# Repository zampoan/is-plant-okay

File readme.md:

# Is-Plant-Okay 🌱?
## Concept
A solar-powered sensor node that uses a low-power camera and a tiny on-board ML model to detect early signs of plant disease. It will be mounted on a stake and its purpose is to continuously watch the same plant or section of crop bed. 

It will periodically take a picture every 4 hours. When it sees trouble, and will send a compact alert packet over LoRa to a base station. The farmer will receive a notification and can inspect or treat the plant before disease spreads.

Dataset to be trained on: https://www.kaggle.com/datasets/vipoooool/new-plant-diseases-dataset

ML model: https://www.nature.com/articles/s41598-025-06452-5

## Hardware
- 🧠 MCU: Arduino Nano 33 BLE Sense Rev2 
- 🔋 LiIon: 7.4 2000mAh
- ☀️ Solar power cells: 0.5W Solar Panel 55x70
- 📷 Camera: CAMERA-OV7670
- 🌡️ Temperature sensor: Arduino Nano 33 BLE Sense Rev2 (onboard HS3003)
- 🌡️ Humidity sensor: Arduino Nano 33 BLE Sense Rev2 (onboard HS3003)
- ~~🌡️ Soil moisture sensor: (Premi um option: RS485)~~
- 🖵 Screen: GRAPHIC DISPLAY TFT RGB 0.96"
- 📡 LoRa: SX1278 RA-02 (Premium option:RYLR998)
- ~~💡 Light Sensor: TSL2591~~
- ~~⚡ UV Sensor: VEML6075~~

## Software
- KiCad 9.0: Schematic diagram drawing & PCB design
- Fusion 360: Case design

# BOM:
| Hardware | Price ($USD) | QTY| Link |
| :------: | :---: | :--: | :--: |
| Arduino Nano 33 BLE Sense Rev 2 | 38.70 | 1 | https://www.digikey.com.au/en/products/detail/arduino/ABX00069/16891607?s=N4IgTCBcDaIIICEAaAGNA2AnCAugXyA
| 0.5W Solar Panel 55x70 | 6.07 | 2 | https://www.digikey.com.au/en/products/detail/seeed-technology-co-ltd/313070004/5488049?gad_source=1&gad_campaignid=22258692864&gbraid=0AAAAADrbLlhlBg2sAgWDGFOENqgOK8itr&gclid=CjwKCAjwuePGBhBZEiwAIGCVS1SN-ztdDNMpsNeNdLkv1kFB5a2T7XsfMUYFsP6d9YNnIU8SkSqs2BoCFH4QAvD_BwE&gclsrc=aw.ds
| CAMERA-OV7670 | 10.25 | 1 | https://www.digikey.com.au/en/products/detail/olimex-ltd/CAMERA-OV7670/21662189?gad_source=1&gad_campaignid=22258692864&gbraid=0AAAAADrbLlj6oJtUsNfVx1vIrDFE3BPZ1&gclid=Cj0KCQjw9JLHBhC-ARIsAK4PhcpgwkVmjjOCHtvELpGt-0733CaYN9VAK-Vob_rOJUDzvEmz226i8pQaAqYBEALw_wcB&gclsrc=aw.ds
| (Camera Alternative) Mini 2MP SPI Camera Module | 25.99 | 1 | https://core-electronics.com.au/mini-2mp-spi-camera-module-for-raspberry-pi-pico.html
| GRAPHIC DISPLAY TFT RGB 0.96" | 12.65| 1 | https://www.digikey.com.au/en/products/detail/adafruit-industries-llc/3533/7386265?_gl=1*b8bl6n*_up*MQ..*_gs*MQ..&gclid=Cj0KCQjw0Y3HBhCxARIsAN7931UClWFcKTlh2fkHoq46prUC8q0JHHVEXAIprqbeCdMH-Q-fxAHX3awaAoXnEALw_wcB&gclsrc=aw.ds&gbraid=0AAAAADrbLlg15LkEfC3epRZwz2bj5q-3L
| LORA BREAKOUT BOARD WITH ANTENNA (SX1278) | 4.12 | 2 |https://www.digikey.com.au/en/products/detail/ai-thinker/RA-01S-KIT/16688834?gad_source=1&gad_campaignid=22326148211&gbraid=0AAAAADrbLlhLN5hmf02vxdAPvPhM4dgSv&gclid=Cj0KCQjw9JLHBhC-ARIsAK4PhcreZk6yLUpkKNMcTffMBGgSn7cPre5FqczhVUk0twJjBSD5UAG_9JgaAqmoEALw_wcB&gclsrc=aw.ds
| (Lora alternative) WIO-E5 MINI DEV BRD STM32WLE5JC | 21.90 | 1 | https://www.digikey.com.au/en/products/detail/seeed-technology-co-ltd/113990939/13926228
| 18650 BATTERY PROTECTION MODULE | 3.9 | 1 | https://www.digikey.com.au/en/products/detail/dfrobot/FIT0869/15997370?gad_source=1&gad_campaignid=22258692864&gbraid=0AAAAADrbLlg15LkEfC3epRZwz2bj5q-3L&gclid=Cj0KCQjw9JLHBhC-ARIsAK4PhcrrSuu6PmTF7blXYFuWj3jp-5aErfmPy3v33kaB2AZqo8hcHLbKMqoaAtIpEALw_wcB&gclsrc=aw.ds
| BATT HOLDER 18650 2 CELL PC PIN | 5.16 | 1 | https://www.digikey.com.au/en/products/detail/mpd-memory-protection-devices/BK-18650-PC4/2330513
| SPI RTC | 27.5 | 1 | https://www.digikey.com.au/en/products/detail/sparkfun-electronics/10160/5318743?gad_source=1&gad_campaignid=17413568847&gbraid=0AAAAADrbLlhQzfR05Cs2nWnXQWMDkBFCG&gclid=Cj0KCQjwl5jHBhDHARIsAB0YqjxafYtF9_N9fzqCNYOEMk2vtOCLYpYshzIofeoXUn1t9SEJgBJjOhwaAnBeEALw_wcB&gclsrc=aw.ds

## Inspiration
https://blog.arduino.cc/2020/06/24/machine-vision-with-low-cost-camera-modules/
https://cdn-learn.adafruit.com/downloads/pdf/adafruit-mini-tft-0-dot-96-inch-180x60-breakout.pdf
https://files.seeedstudio.com/products/317990687/res/LoRa-E5%20module%20datasheet_V1.0.pdf

# Project Timeline
## Stage 0: Project Conceptualization
Stage 0 focuses on identifying the key skills to develop for this project. My goal was to deepen my understanding of wireless communication and explore how to integrate machine learning into embedded devices. I was particularly interested in how these technologies could support farmers and forest rangers in monitoring crops and plants across large, diverse environment. My goal was to make it as cheap as possible and require little human interaction once placed.

## Stage 1a: Development board stage
Stage 1a involves selecting different components to interface with each other. The most important element was the microcontroller, and I choose the Arduino Nano 33 BLE Sense V2 for its built in sensor capabilities, community support and access to TF-lite as an edge-ml solution.

The next was selecting a camera, I needed a camera that I could use off the shelf quickly for developing. Originally HM0360-MWA-00FP963 was selected, but I found it difficult to find a dev board for it. So the OV7670 was selected instead.

Similiar to the camera, SX1278 RA-02 module was selected because a dev board was available, and the DS3234 was chosen because SPI is the common protocol that is being used.

## Stage 1b: Developing the model
The model that is being used is based of the paper: [AI and IoT-powered edge device optimized for crop pest and disease detection](https://www.nature.com/articles/s41598-025-06452-5) and is called Tiny-LiteNet. It was chosen because of its use case matched  and identifiable metrics used to train and test the model. 

The model is made from scratch and is trained on a different dataset and uses a pretrained MobileNetv2 model as a teacher model. Tiny-LiteNet utilises six squeeze-and-excitation (SE) depthwise blocks to enhance feature representation, reduce compute cost and improve accuracy combined. The size of this model is 1.2Mb.

Tiny-LiteNet architecture:

## Stage 2a: PCB design

## Stage 2b: CAD design

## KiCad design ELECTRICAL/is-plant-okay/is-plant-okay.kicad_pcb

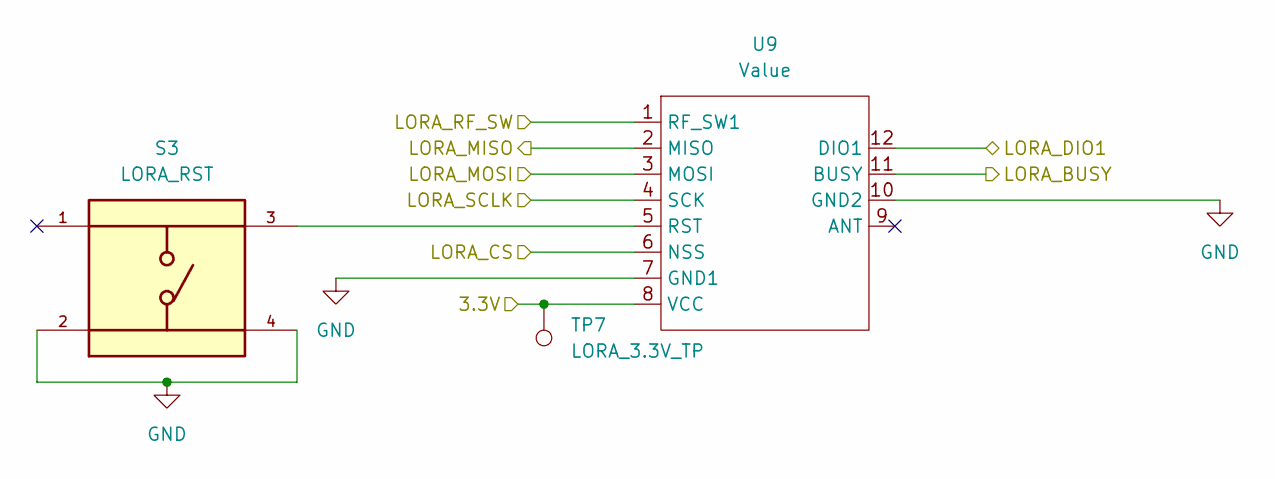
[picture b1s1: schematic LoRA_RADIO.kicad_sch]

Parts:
S3: LORA_RST; SW_TS04-66-55-BK-260-SMT; MFG PART # TS04-66-55-BK-260-SMT
TP7: LORA_3.3V_TP; TestPoint_Keystone_5000-5004_Miniature
U9: Value; Wio-SX1262 PCB Package; MFG PART # 114993390

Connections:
/3.3V: TP7.1, U9.8 (VCC); also elsewhere on the board
/LORA_BUSY: U9.11 (BUSY); also elsewhere on the board
/LORA_CS: U9.6 (NSS); also elsewhere on the board
/LORA_DIO1: U9.12 (DIO1); also elsewhere on the board
/LORA_MISO: U9.2 (MISO); also elsewhere on the board
/LORA_MOSI: U9.3 (MOSI); also elsewhere on the board
/LORA_RF_SW: U9.1 (RF_SW1); also elsewhere on the board
/LORA_SCLK: U9.4 (SCK); also elsewhere on the board
GND: S3.2, S3.4, U9.7 (GND1), U9.10 (GND2); also elsewhere on the board
unnamed: S3.3, U9.5 (RST)

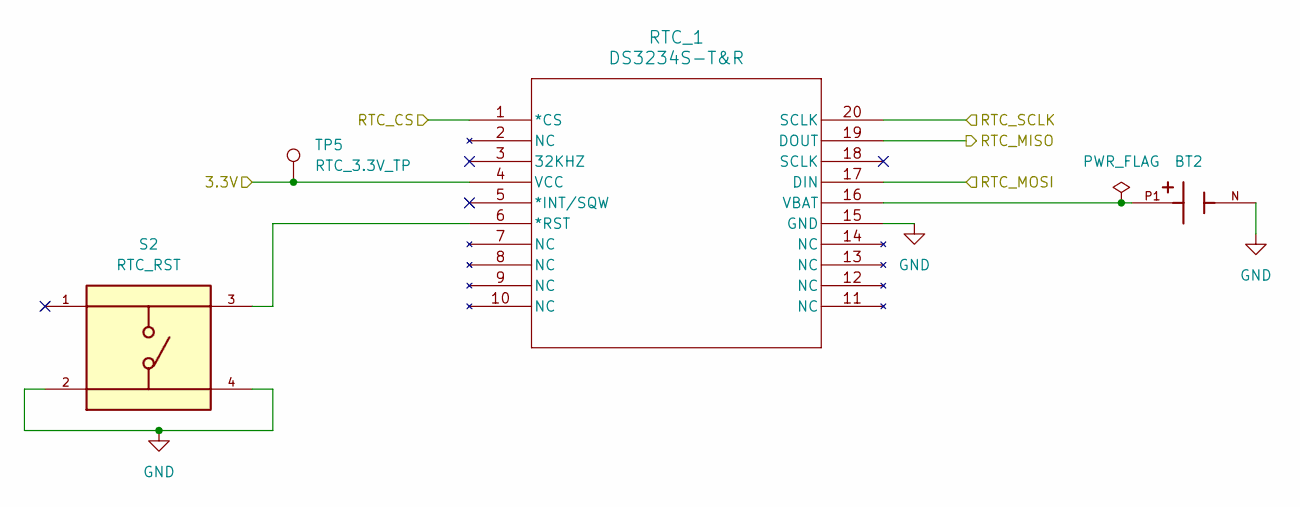
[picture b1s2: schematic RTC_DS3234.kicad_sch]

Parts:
BT2: BAT-HLD-003-SMT; BAT_BAT-HLD-003-SMT; MFG PART # BAT-HLD-003-SMT
RTC_1: DS3234S-T&R; 21-0042O_W20-H2_MXM-L; MFG PART # DS3234S#
S2: RTC_RST; SW_TS04-66-55-BK-260-SMT; MFG PART # TS04-66-55-BK-260-SMT
TP5: RTC_3.3V_TP; TestPoint_Keystone_5000-5004_Miniature

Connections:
/3.3V: RTC_1.4 (VCC), TP5.1; also elsewhere on the board
/LORA_MISO: RTC_1.19 (DOUT); also elsewhere on the board
/LORA_MOSI: RTC_1.17 (DIN); also elsewhere on the board
/LORA_SCLK: RTC_1.20 (SCLK); also elsewhere on the board
/RTC_CS: RTC_1.1 (*CS); also elsewhere on the board
GND: BT2.N, RTC_1.15 (GND), S2.2, S2.4; also elsewhere on the board
unnamed: RTC_1.6 (*RST), S2.3
unnamed: BT2.P1, RTC_1.16 (VBAT)

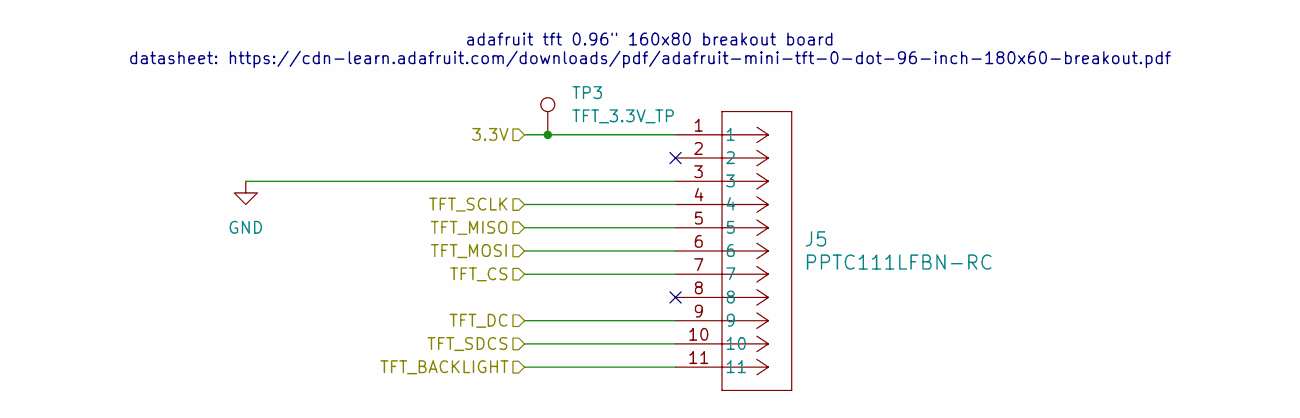
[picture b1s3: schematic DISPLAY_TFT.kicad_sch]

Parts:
J5: PPTC111LFBN-RC; CONN11_PPPN111_SUL; MFG PART # PPTC111LFBN-RC
TP3: TFT_3.3V_TP; TestPoint_Keystone_5000-5004_Miniature

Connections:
/3.3V: J5.1, TP3.1; also elsewhere on the board
/BACKLIGHT: J5.11; also elsewhere on the board
/LORA_MISO: J5.5; also elsewhere on the board
/LORA_MOSI: J5.6; also elsewhere on the board
/LORA_SCLK: J5.4; also elsewhere on the board
/TFT_CS: J5.7; also elsewhere on the board
/TFT_DC: J5.9; also elsewhere on the board
/TFT_SDCS: J5.10; also elsewhere on the board
GND: J5.3; also elsewhere on the board

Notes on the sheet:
adafruit tft 0.96" 160x80 breakout board datasheet: https://cdn-learn.adafruit.com/downloads/pdf/adafruit-mini-tft-0-dot-96-inch-180x60-breakout.pdf

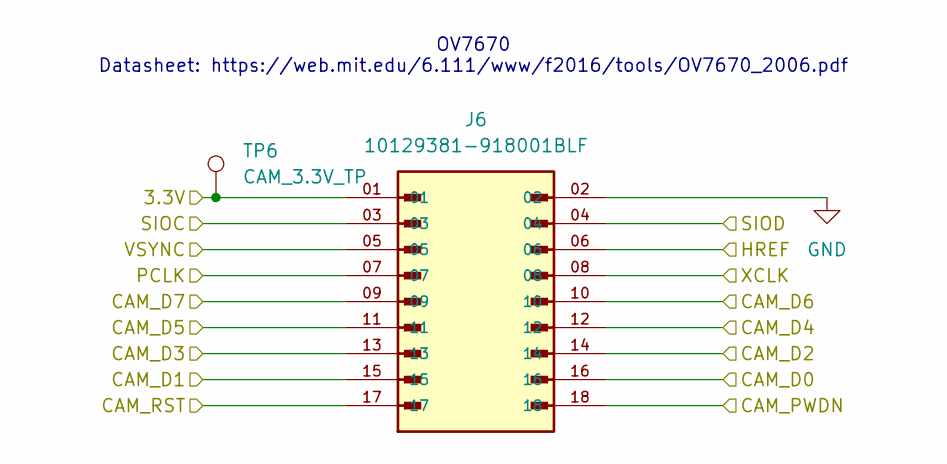
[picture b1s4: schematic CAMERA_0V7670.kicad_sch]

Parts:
J6: 10129381-918001BLF; AMPHENOL_10129381-918001BLF; MFG PART # 10129381-918001BLF
TP6: CAM_3.3V_TP; TestPoint_Keystone_5000-5004_Miniature

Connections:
/3.3V: J6.01, TP6.1; also elsewhere on the board
/CAM_D0: J6.16; also elsewhere on the board
/CAM_D1: J6.15; also elsewhere on the board
/CAM_D2: J6.14; also elsewhere on the board
/CAM_D3: J6.13; also elsewhere on the board
/CAM_D4: J6.12; also elsewhere on the board
/CAM_D5: J6.11; also elsewhere on the board
/CAM_D6: J6.10; also elsewhere on the board
/CAM_D7: J6.09; also elsewhere on the board
/CAM_PWDN: J6.18; also elsewhere on the board
/CAM_RST: J6.17; also elsewhere on the board
/HREF: J6.06; also elsewhere on the board
/PCLK: J6.07; also elsewhere on the board
/SIOC: J6.03; also elsewhere on the board
/SIOD: J6.04; also elsewhere on the board
/VSYNC: J6.05; also elsewhere on the board
/XCLK: J6.08; also elsewhere on the board
GND: J6.02; also elsewhere on the board

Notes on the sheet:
OV7670 Datasheet: https://web.mit.edu/6.111/www/f2016/tools/OV7670_2006.pdf

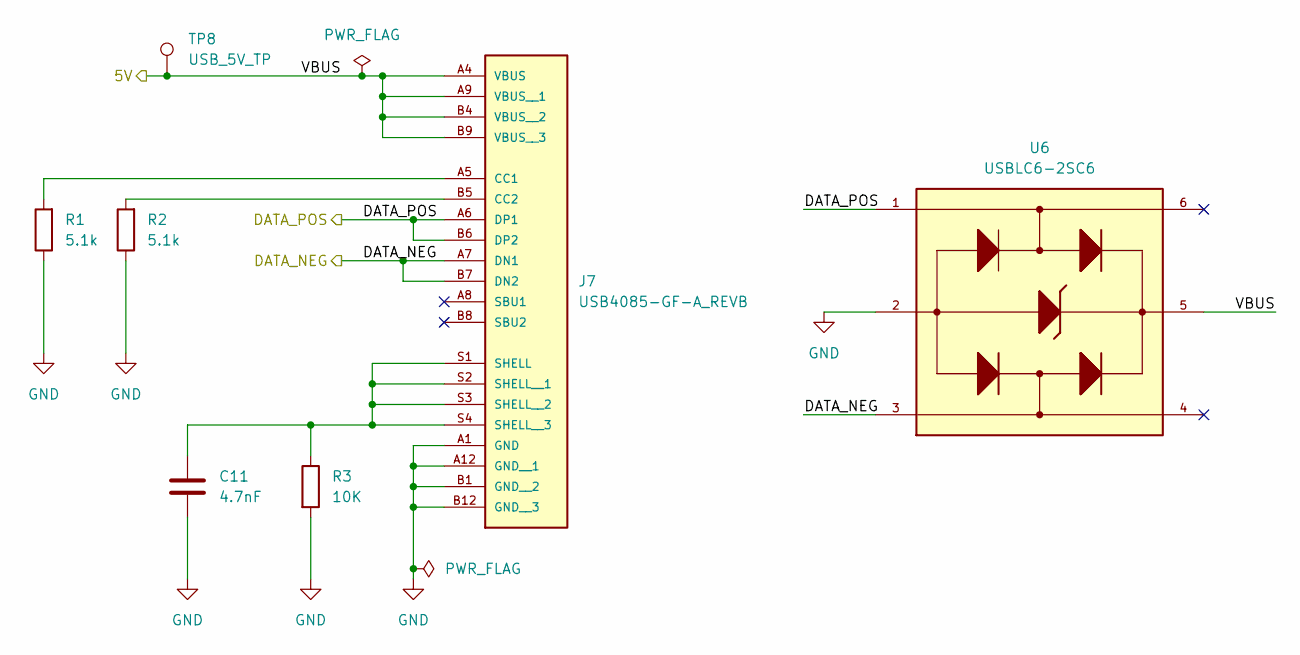
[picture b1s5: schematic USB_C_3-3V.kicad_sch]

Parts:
C11: 4.7nF; CAPC1005X55N; MFG PART # CL05B104KO5NNNC
J7: USB4085-GF-A_REVB; GCT_USB4085-GF-A_REVB; MFG PART # USB4085-GF-A
R1, R2: 5.1k; RC0805JR-075K1L; MFG PART # RC0805JR-075K1L
R3: 10K; RC0805FR-7W10KL; MFG PART # RC0805FR-7W10KL
TP8: USB_5V_TP; TestPoint_Keystone_5000-5004_Miniature
U6: USBLC6-2SC6; SOT95P280X145-6N; MFG PART # USBLC6-2SC6

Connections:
/5V: J7.A4 (VBUS), J7.A9 (VBUS__1), J7.B4 (VBUS__2), J7.B9 (VBUS__3), TP8.1, U6.5; also elsewhere on the board
/DATA_NEG: J7.A7 (DN1), J7.B7 (DN2), U6.3; also elsewhere on the board
/DATA_POS: J7.A6 (DP1), J7.B6 (DP2), U6.1; also elsewhere on the board
GND: C11.2, J7.A1 (GND), J7.A12 (GND__1), J7.B1 (GND__2), J7.B12 (GND__3), R1.1, R2.1, R3.2, U6.2; also elsewhere on the board
unnamed: J7.A5 (CC1), R1.2
unnamed: J7.B5 (CC2), R2.2
unnamed: C11.1, J7.S1 (SHELL), J7.S2 (SHELL__1), J7.S3 (SHELL__2), J7.S4 (SHELL__3), R3.1

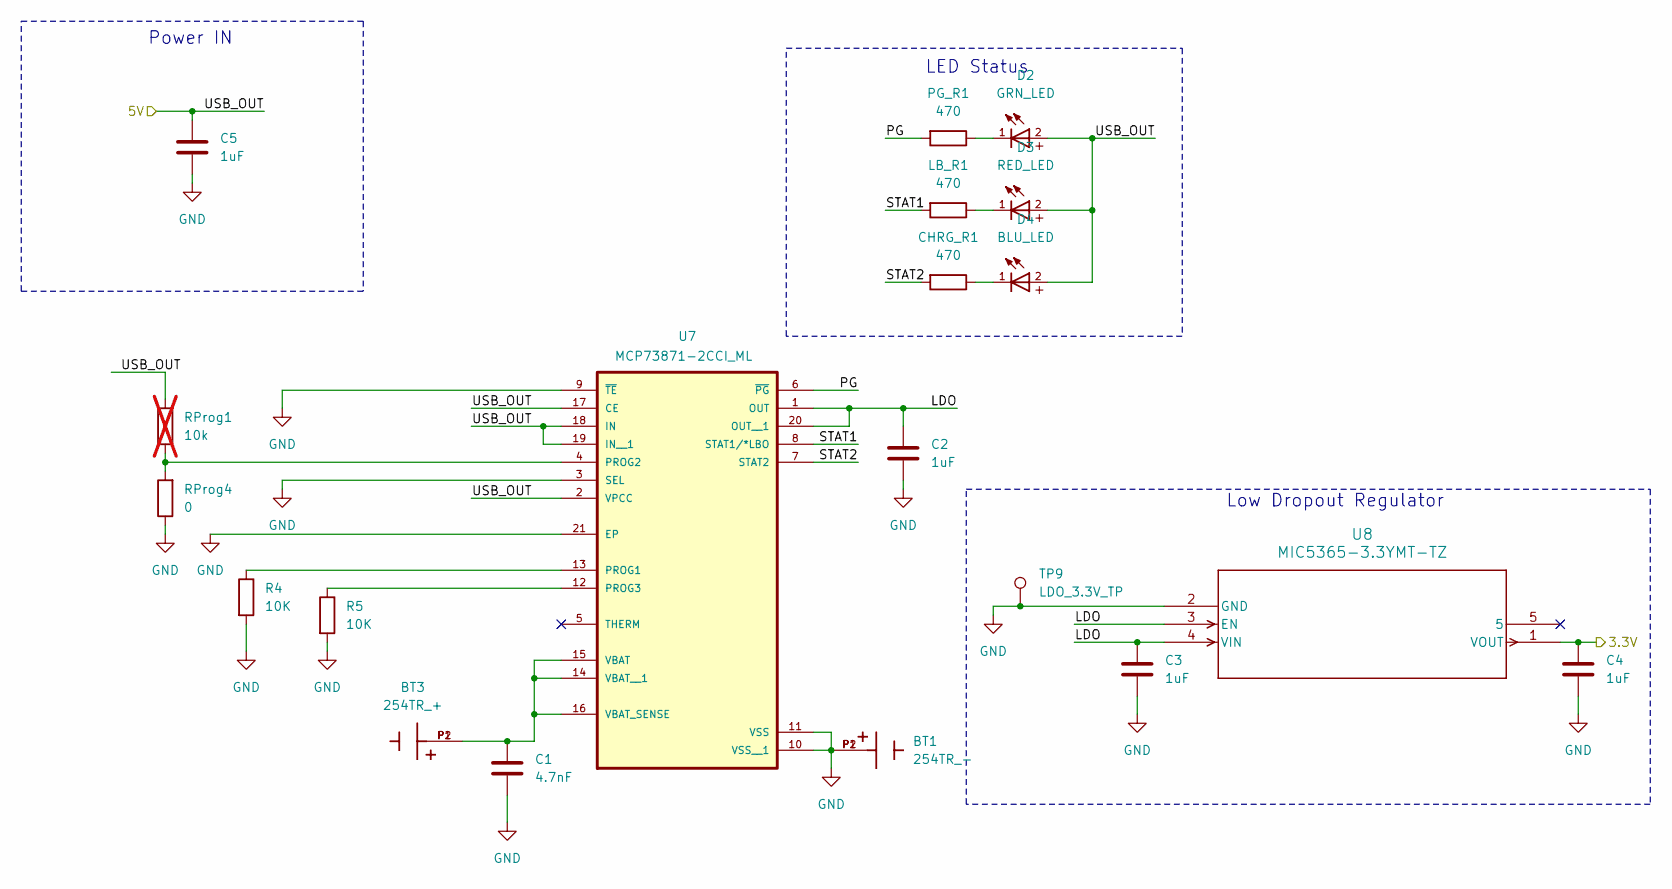
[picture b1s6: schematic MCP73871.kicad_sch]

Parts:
BT1: 254TR_-; BAT_254TR; MFG PART # 254TR
BT3: 254TR_+; BAT_254TR; MFG PART # 254TR
C1: 4.7nF; CAPC1005X55N; MFG PART # CL05B104KO5NNNC
C2, C3, C4, C5: 1uF; CAPC3216X180N; MFG PART # CL31B105KBHNNNE
CHRG_R1: 470; RESC2012X65N
D2: GRN_LED; 150120GS75000; MFG PART # 150120GS75000
D3: RED_LED; 150120GS75000; MFG PART # 150120RS75000
D4: BLU_LED; 150120GS75000; MFG PART # 150120BS75000
LB_R1: 470; RESC2012X65N
PG_R1: 470; RESC2012X65N
R4, R5: 10K; RC0805FR-7W10KL; MFG PART # RC0805FR-7W10KL
RProg1: 10k; RES_ZOR25_6P3X2P3_YAG; MFG PART # ZOR-25-B-52-0R; not fitted
RProg4: 0; RES_ZOR25_6P3X2P3_YAG; MFG PART # ZOR-25-B-52-0R
TP9: LDO_3.3V_TP; TestPoint_Keystone_5000-5004_Miniature
U7: MCP73871-2CCI_ML; QFN50P400X400X100-21N; MFG PART # MCP73871-2CCI/ML
U8: MIC5365-3.3YMT-TZ; TMLF-4_MCH; MFG PART # MIC5365-3.3YMT-TZ

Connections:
/3.3V: C4.1, U8.1 (VOUT); also elsewhere on the board
/5V: C5.1, D2.2, D3.2, D4.2, RProg1.2, U7.2 (VPCC), U7.17 (CE), U7.18 (IN), U7.19 (IN__1); also elsewhere on the board
/MCP73871/LDO: C2.1, C3.1, U7.1 (OUT), U7.20 (OUT__1), U8.3 (EN), U8.4 (VIN)
/MCP73871/PG: PG_R1.2, U7.6 (~PG)
/MCP73871/STAT1: LB_R1.2, U7.8 (STAT1/*LBO)
/MCP73871/STAT2: CHRG_R1.2, U7.7 (STAT2)
GND: BT1.P1, BT1.P2, C1.2, C2.2, C3.2, C4.2, C5.2, R4.2, R5.2, RProg4.1, TP9.1, U7.3 (SEL), U7.9 (~TE), U7.10 (VSS__1), U7.11 (VSS), U7.21 (EP), U8.2 (GND); also elsewhere on the board
unnamed: CHRG_R1.1, D4.1
unnamed: D2.1, PG_R1.1
unnamed: D3.1, LB_R1.1
unnamed: R4.1, U7.13 (PROG1)
unnamed: RProg1.1, RProg4.2, U7.4 (PROG2)
unnamed: R5.1, U7.12 (PROG3)
unnamed: BT3.P1, BT3.P2, C1.1, U7.14 (VBAT__1), U7.15 (VBAT), U7.16 (VBAT_SENSE)

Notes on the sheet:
Low Dropout Regulator
LED Status
Power IN

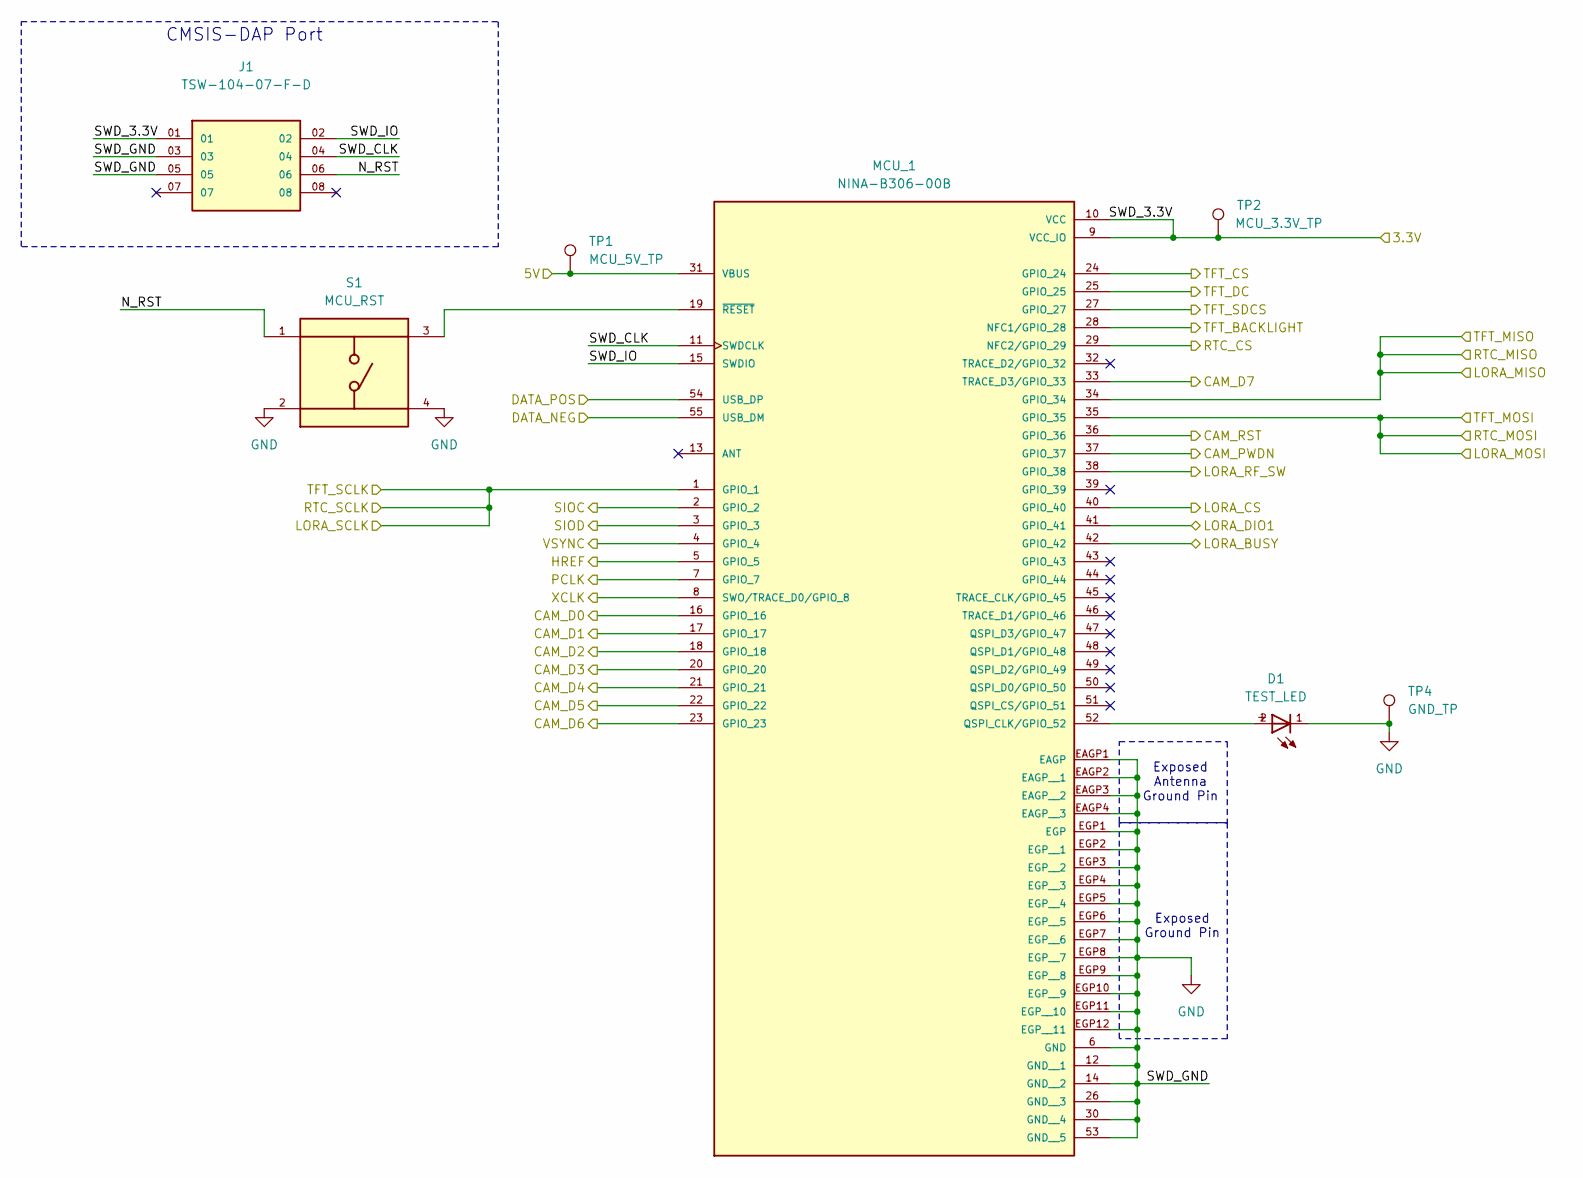
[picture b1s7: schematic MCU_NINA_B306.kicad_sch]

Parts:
D1: TEST_LED; 150120GS75000; MFG PART # 150120GS75000
J1: TSW-104-07-F-D; SAMTEC_TSW-104-07-F-D
MCU_1: NINA-B306-00B; XCVR_NINA-B306-00B; MFG PART # NINA-B306-01B
S1: MCU_RST; SW_TS04-66-55-BK-260-SMT; MFG PART # TS04-66-55-BK-260-SMT
TP1: MCU_5V_TP; TestPoint_Keystone_5000-5004_Miniature
TP2: MCU_3.3V_TP; TestPoint_Keystone_5000-5004_Miniature
TP4: GND_TP; TestPoint_Keystone_5000-5004_Miniature

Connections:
/3.3V: J1.01, MCU_1.9 (VCC_IO), MCU_1.10 (VCC), TP2.1; also elsewhere on the board
/5V: MCU_1.31 (VBUS), TP1.1; also elsewhere on the board
/BACKLIGHT: MCU_1.28 (NFC1/GPIO_28); also elsewhere on the board
/CAM_D0: MCU_1.16 (GPIO_16); also elsewhere on the board
/CAM_D1: MCU_1.17 (GPIO_17); also elsewhere on the board
/CAM_D2: MCU_1.18 (GPIO_18); also elsewhere on the board
/CAM_D3: MCU_1.20 (GPIO_20); also elsewhere on the board
/CAM_D4: MCU_1.21 (GPIO_21); also elsewhere on the board
/CAM_D5: MCU_1.22 (GPIO_22); also elsewhere on the board
/CAM_D6: MCU_1.23 (GPIO_23); also elsewhere on the board
/CAM_D7: MCU_1.33 (TRACE_D3/GPIO_33); also elsewhere on the board
/CAM_PWDN: MCU_1.37 (GPIO_37); also elsewhere on the board
/CAM_RST: MCU_1.36 (GPIO_36); also elsewhere on the board
/DATA_NEG: MCU_1.55 (USB_DM); also elsewhere on the board
/DATA_POS: MCU_1.54 (USB_DP); also elsewhere on the board
/HREF: MCU_1.5 (GPIO_5); also elsewhere on the board
/LORA_BUSY: MCU_1.42 (GPIO_42); also elsewhere on the board
/LORA_CS: MCU_1.40 (GPIO_40); also elsewhere on the board
/LORA_DIO1: MCU_1.41 (GPIO_41); also elsewhere on the board
/LORA_MISO: MCU_1.34 (GPIO_34); also elsewhere on the board
/LORA_MOSI: MCU_1.35 (GPIO_35); also elsewhere on the board
/LORA_RF_SW: MCU_1.38 (GPIO_38); also elsewhere on the board
/LORA_SCLK: MCU_1.1 (GPIO_1); also elsewhere on the board
/MCU_NINA_B306/N_RST: J1.06, S1.1
/MCU_NINA_B306/SWD_CLK: J1.04, MCU_1.11 (SWDCLK)
/MCU_NINA_B306/SWD_IO: J1.02, MCU_1.15 (SWDIO)
/PCLK: MCU_1.7 (GPIO_7); also elsewhere on the board
/RTC_CS: MCU_1.29 (NFC2/GPIO_29); also elsewhere on the board
/SIOC: MCU_1.2 (GPIO_2); also elsewhere on the board
/SIOD: MCU_1.3 (GPIO_3); also elsewhere on the board
/TFT_CS: MCU_1.24 (GPIO_24); also elsewhere on the board
/TFT_DC: MCU_1.25 (GPIO_25); also elsewhere on the board
/TFT_SDCS: MCU_1.27 (GPIO_27); also elsewhere on the board
/VSYNC: MCU_1.4 (GPIO_4); also elsewhere on the board
/XCLK: MCU_1.8 (SWO/TRACE_D0/GPIO_8); also elsewhere on the board
GND: D1.1, J1.03, J1.05, MCU_1.6 (GND), MCU_1.12 (GND__1), MCU_1.14 (GND__2), MCU_1.26 (GND__3), MCU_1.30 (GND__4), MCU_1.53 (GND__5), MCU_1.EAGP1 (EAGP), MCU_1.EAGP2 (EAGP__1), MCU_1.EAGP3 (EAGP__2), MCU_1.EAGP4 (EAGP__3), MCU_1.EGP1 (EGP), MCU_1.EGP2 (EGP__1), MCU_1.EGP3 (EGP__2), MCU_1.EGP4 (EGP__3), MCU_1.EGP5 (EGP__4), MCU_1.EGP6 (EGP__5), MCU_1.EGP7 (EGP__6), MCU_1.EGP8 (EGP__7), MCU_1.EGP9 (EGP__8), MCU_1.EGP10 (EGP__9), MCU_1.EGP11 (EGP__10), MCU_1.EGP12 (EGP__11), S1.2, S1.4, TP4.1; also elsewhere on the board
unnamed: D1.2, MCU_1.52 (QSPI_CLK/GPIO_52)
unnamed: MCU_1.19 (~RESET), S1.3

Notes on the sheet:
Exposed Antenna Ground Pin
Exposed Ground Pin
CMSIS-DAP Port

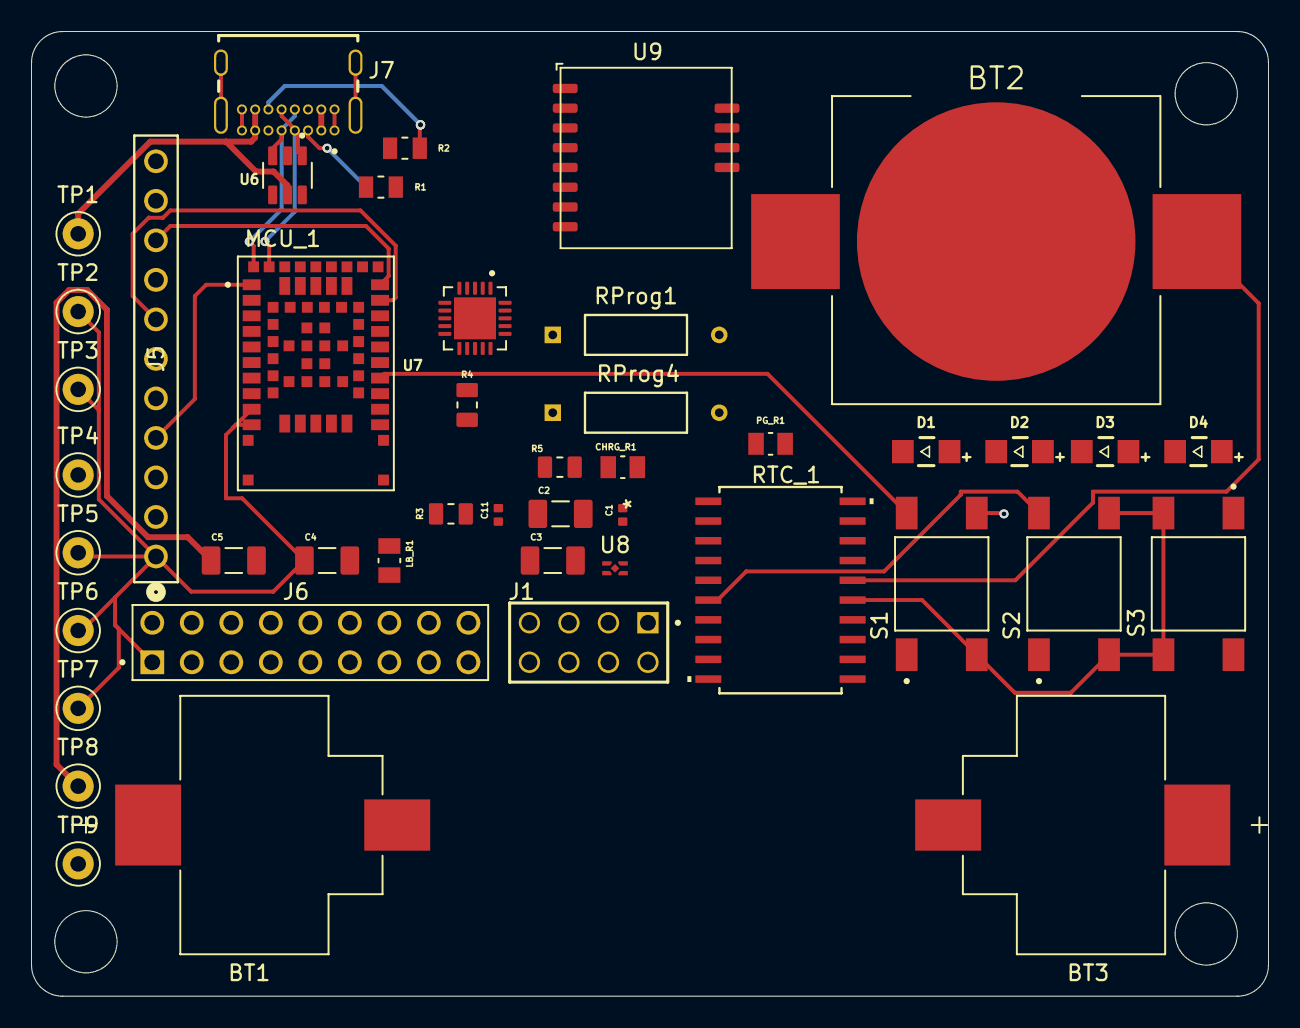
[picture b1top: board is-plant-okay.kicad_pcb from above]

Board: 2 copper layers, 79.5 x 62.0 mm, 45 parts (0 on the bottom side), 55 nets.

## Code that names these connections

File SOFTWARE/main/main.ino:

/*
    Before starting, install following libraries:
        - adafruit_gfx
        - adafruit_st7735
        - arduino_hs300x
        - arduino_bmi270_bmm150
        - arduino_LPS22HB
        - ds3231

*/
#include <SPI.h>
#include <Adafruit_GFX.h>
#include <Adafruit_ST7735.h> // using 0.96" 160x80 tft display
#include <Arduino_HS300x.h>
#include <DS3231.h>
#include <time.h>

// Pinouts
#define CAM_D0 D0
#define CAM_D1 D1
#define CAM_D2 D2
#define CAM_D3 D3
#define CAM_D4 D4
#define CAM_D5 D5
#define CAM_D6 D6
#define CAM_D7 D7
#define CAM_VSYNC D8
#define CAM_XCLK D9 
#define CAM_HREF D10
#define TFT_DC A0
#define LORA_CS A1
#define LORA_RST A2
#define TFT_CS A3
#define CAM_SIOD A4
#define CAM_SIOC A5
#define RTC_CS A6
#define CAM_PCLK A7
#define UNUSED_PIN -1

#define DEBUG
#ifdef DEBUG
    #define DEBUG_PRINT(x) Serial.print(x)
    #define DEBUG_PRINTLN(x) Serial.println(x) 
#else
    #define DEBUG_PRINT(x) 
    #define DEBUG_PRINTLN(x) 
#endif

// tft screen
Adafruit_ST7735 tft = Adafruit_ST7735(TFT_CS, TFT_DC, UNUSED_PIN);

// DS3231 rtc
// RTClib myRTC;
// DateTime now = myRTC.now();

// temperature and humidity sensor
float old_temp = 0;
float old_hum = 0;

void showTemperatureHumidity(void){
    float temperature = HS300x.readTemperature();
    float humidity = HS300x.readHumidity();

    if (abs(old_temp - temperature) >= 0.5 || abs(old_hum - humidity) >= 1){
        DEBUG_PRINT("Temperature: ");
        DEBUG_PRINTLN(temperature);

        DEBUG_PRINT("Humidity: ");
        DEBUG_PRINTLN(humidity);
        DEBUG_PRINTLN(" %");

        delay(500);
    }
}

void drawText(char *text, uint16_t textColor, uint8_t xCursor, uint8_t yCursor){
    tft.setRotation(1);
    tft.setCursor(xCursor, yCursor);
    tft.setTextColor(textColor, ST7735_BLACK);
    tft.setTextWrap(true);
    tft.print(text);
}

void setup() {
    Serial.begin(11600);
    SPI.begin();

    if (!HS300x.begin()){
        DEBUG_PRINTLN("Failed to init HS300x!");
    } 

    // Camera Pins
    pinMode(CAM_SIOD, INPUT); // Serial ubterface data I/o
    pinMode(CAM_SIOC, INPUT); // Serial clock
    pinMode(CAM_D0, OUTPUT); 
    pinMode(CAM_D1, OUTPUT);
    pinMode(CAM_D2, OUTPUT);
    pinMode(CAM_D3, OUTPUT);
    pinMode(CAM_D4, OUTPUT);
    pinMode(CAM_D5, OUTPUT);
    pinMode(CAM_D6, OUTPUT);
    pinMode(CAM_D7, OUTPUT);
    pinMode(CAM_VSYNC, OUTPUT); // vertical sync output
    pinMode(CAM_HREF, OUTPUT); // href output
    pinMode(CAM_PCLK, OUTPUT); // pixel clock output
    pinMode(CAM_XCLK, OUTPUT); // system clock output


    // LoRa Module Pins
    pinMode(LORA_CS, OUTPUT);
    pinMode(LORA_RST, OUTPUT);

    // TFT Screen Pins
    pinMode(TFT_CS, OUTPUT);
    tft.initR(INITR_MINI160x80);
    tft.fillScreen(ST7735_BLACK);

    // RTC Pins
    pinMode(RTC_CS, OUTPUT);

    delay(3000);
    DEBUG_PRINTLN("Finished Setup...");
}

void loop(){
    Serial.println("1");
    //drawText("Hello World!", ST7735_WHITE, 0, 50);
    delay(1000);
    // // showTemperatureHumidity();
    Serial.println("2");

    // Serial.println(now.year(), DEC);
    Serial.println(3);
    // Serial.println("WHY ");
}

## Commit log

2025-09-17 first draft
2025-09-17 fleshed out readme
2025-09-19 Add readme.md
2025-09-19 add bq24650 schematic
2025-09-19 add bq77915 module
2025-09-29 add BOM, add changes to MCU
2025-09-30 add downloaded dataset
2025-10-01 add downloaded dataset, add model creation
2025-10-02 changed oled display
2025-10-03 add trained model
2025-10-04 add mcu environment
2025-10-05 add tflite model
2025-10-07 add arduino code
2025-10-08 add pinout and bom alternative
2025-10-09 feat: added pins for mcu
2025-10-09 feat: added spi to bom, added pin out
2025-10-10 feat: added weights, added model, added earlystopping
2025-10-13 docs: add stages 0, 1a, 1b to readme
2025-10-30 feat: minor pin fixes, add camera moduel to schematic
2025-10-31 feat: add lora, rtc, coin cell, tft screen to schematic
2025-11-27 feat: add pins to setup function
2025-11-28 feat: add humidity function
2025-12-05 feat: add a way to display text on screen
2025-12-09 feat: add rtcDS3234
2025-12-10 feat: add schematic and footprints for ds3234 and ninab306
2025-12-10 feat: add lora
2025-12-11 feat: add coin cell footprint
2025-12-13 feat: add header pins for tft and camera
2025-12-13 feat: add usb and esd protection device
2025-12-13 feat: add ldo and power management IC
2025-12-15 feat: add pins for mcu
2025-12-16 feat: add pins for bootloader programmer
2025-12-17 feat: finished schematics
2025-12-17 feat: add resistor footprint
2025-12-18 feat: add remaining resistor, capacitor footprints
2026-01-10 feat: add definitions to pcb
